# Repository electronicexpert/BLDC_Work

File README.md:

# BLDC_Work
some experiments with BLDC Motors and drivers

Thanks to Gil Vargas for the inspiration. I tried out some motors and controllers. In the end I build one myself, very close to Gil's draft.

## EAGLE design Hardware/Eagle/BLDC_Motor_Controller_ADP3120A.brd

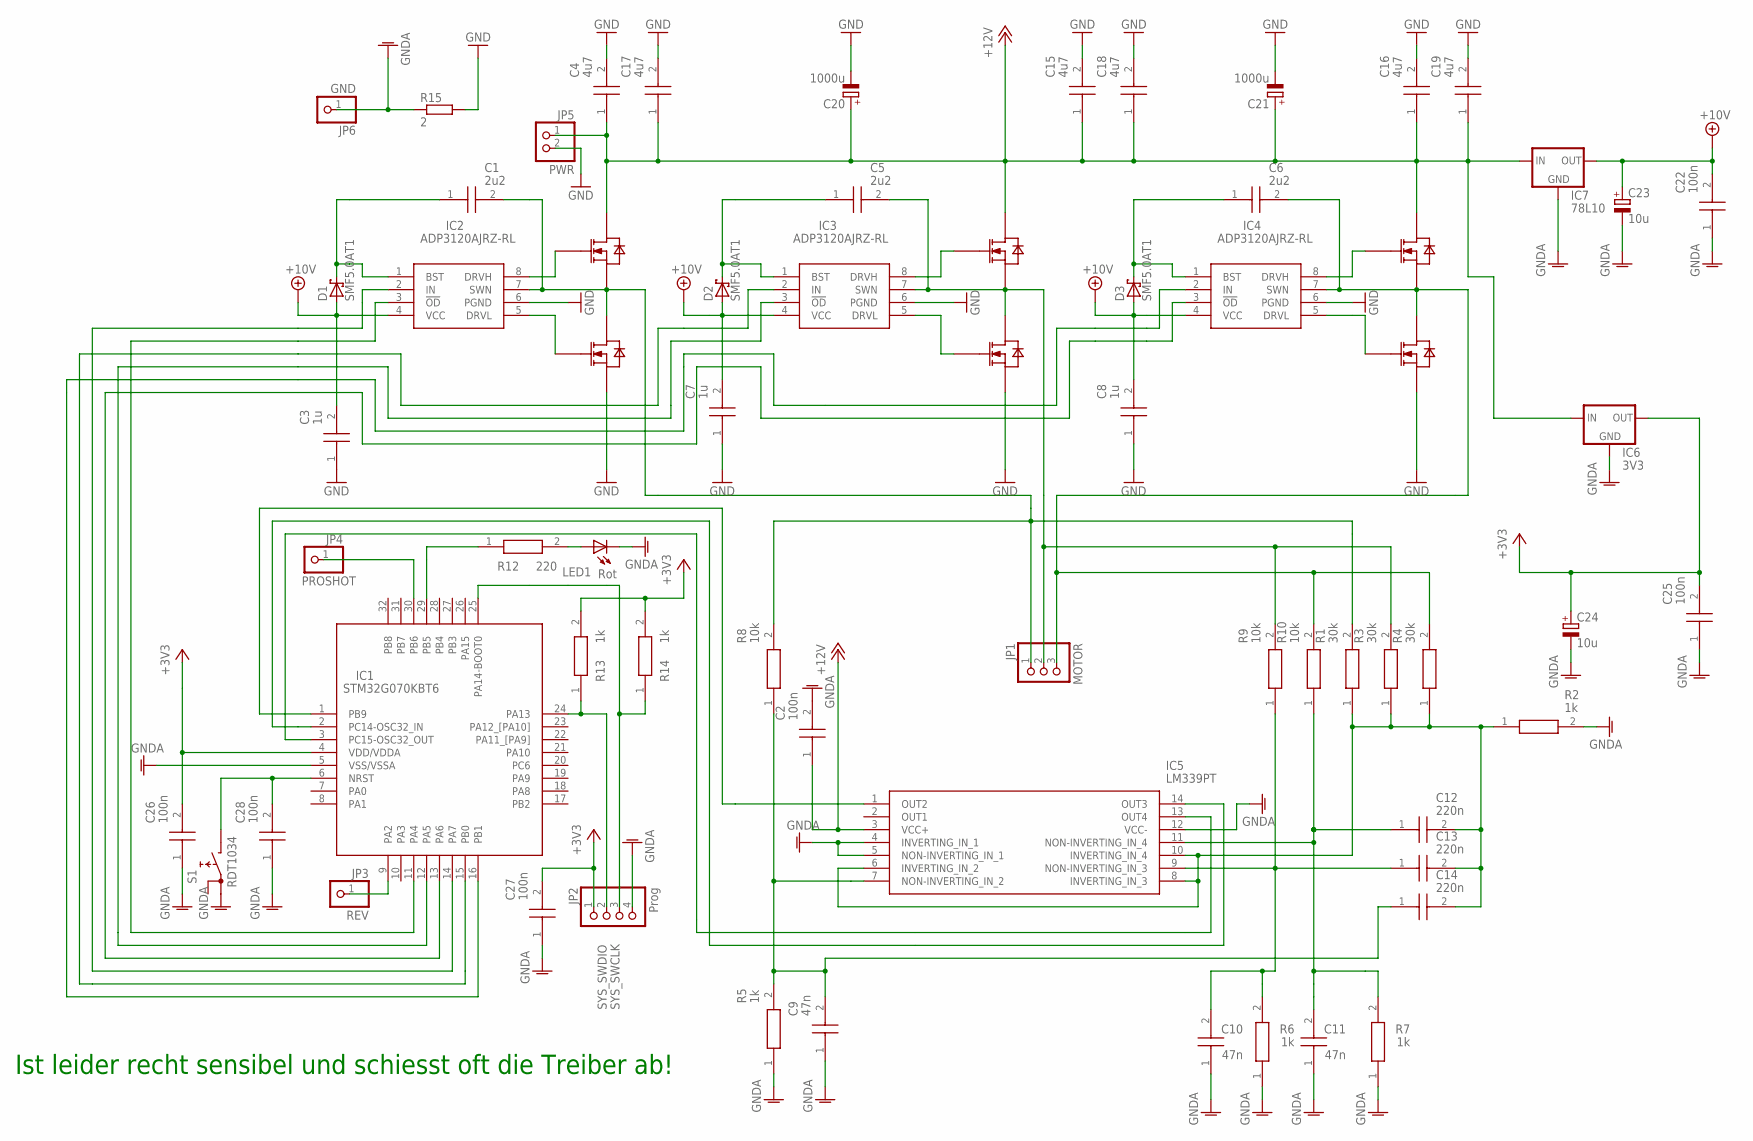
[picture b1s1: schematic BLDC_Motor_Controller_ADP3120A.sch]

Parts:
C1, C5, C6: 2u2; CAPC2012X135N
C2, C22, C25, C26, C27, C28: 100n; CAPC2012X145N
C3, C7, C8: 1u; GRM31X
C4, C15, C16, C17, C18, C19: 4u7; GRM31X
C9, C10, C11: 47n; CAPC2012X145N
C12, C13, C14: 220n; CAPC2012X145N
C20, C21: 1000u; 150CLZ-0810
C23, C24: 10u; SMC_C
D1, D2, D3: SMF5.0AT1; SOD123FL
IC1: STM32G070KBT6; QFP80P900X900X160-32N
IC2, IC3, IC4: ADP3120AJRZ-RL; SOIC127P600X175-8N
IC5: LM339PT; SOP65P640X120-14N
IC6: 3V3; SOT89R
IC7: 78L10; SOT89R
JP1: MOTOR; 1X03
JP2: Prog; 1X04
JP3: REV; 1X01
JP4: PROSHOT; 1X01
JP5: PWR; 1X02
JP6: GND; 1X01
LED1: Rot; SML0805
Q1, Q2, Q3, Q4, Q5, Q6: IRFR1205TRPBF; TO229P991X239-3_4N
R1, R3, R4: 30k; ERJUP6
R2, R5, R6, R7, R13, R14: 1k; ERJUP6
R8, R9, R10: 10k; ERJUP6
R12: 220; ERJUP6
R15: 2; R2012
S1: RDT1034

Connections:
+3V3: C24.+, C25.2, C26.2, C27.2, IC1.4 (VDD/VDDA), IC6.3 (OUT), JP2.1, R13.2, R14.2
+10V: C3.2, C7.2, C8.2, C22.2, C23.+, D1.A, D2.A, D3.A, IC2.4 (VCC), IC3.4 (VCC), IC4.4 (VCC), IC7.3 (OUT)
+12V: C2.1, C4.1, C15.1, C16.1, C17.1, C18.1, C19.1, C20.+, C21.+, IC5.3 (VCC+), IC6.2 (IN), IC7.2 (IN), JP5.1, Q1.4 (DRAIN), Q3.4 (DRAIN), Q5.4 (DRAIN)
BEMF_U: C9.2, C14.1, IC5.7 (NON-INVERTING_IN_2), R5.2, R8.1
BEMV_GND: C12.2, C13.2, C14.2, IC5.6 (INVERTING_IN_2), IC5.8 (INVERTING_IN_3), IC5.10 (INVERTING_IN_4), R1.1, R2.1, R3.1, R4.1
BEMV_V: C10.2, C13.1, IC5.9 (NON-INVERTING_IN_3), R6.2, R9.1
BEMV_W: C11.2, C12.1, IC5.11 (NON-INVERTING_IN_4), R7.2, R10.1
GND: C3.1, C4.2, C7.1, C8.1, C15.2, C16.2, C17.2, C18.2, C19.2, C20.-, C21.-, IC2.6 (PGND), IC3.6 (PGND), IC4.6 (PGND), JP5.2, Q2.3 (SOURCE), Q4.3 (SOURCE), Q6.3 (SOURCE), R15.2
GNDA: C2.2, C9.1, C10.1, C11.1, C22.1, C23.-, C24.-, C25.1, C26.1, C27.1, C28.1, IC1.5 (VSS/VSSA), IC5.4 (INVERTING_IN_1), IC5.5 (NON-INVERTING_IN_1), IC5.12 (VCC-), IC6.1 (GND), IC7.1 (GND), JP2.4, JP6.1, LED1.C, R2.2, R5.1, R6.1, R7.1, R15.1, S1.A1
IN_U: IC1.14 (PA7), IC2.2 (IN)
IN_V: IC1.15 (PB0), IC3.2 (IN)
IN_W: IC1.16 (PB1), IC4.2 (IN)
unnamed: LED1.A, R12.2
unnamed: IC3.8 (DRVH), Q3.1 (GATE)
unnamed: IC3.5 (DRVL), Q4.1 (GATE)
unnamed: IC2.8 (DRVH), Q1.1 (GATE)
unnamed: IC2.5 (DRVL), Q2.1 (GATE)
unnamed: IC4.8 (DRVH), Q5.1 (GATE)
unnamed: IC4.5 (DRVL), Q6.1 (GATE)
unnamed: C1.1, D1.C, IC2.1 (BST)
unnamed: IC1.29 (PB5), R12.1
unnamed: C5.1, D2.C, IC3.1 (BST)
unnamed: IC1.9 (PA2), JP3.1
unnamed: C6.1, D3.C, IC4.1 (BST)
unnamed: IC1.2 (PC14-OSC32_IN), IC5.14 (OUT3)
unnamed: C28.2, IC1.6 (NRST), S1.B
unnamed: IC1.1 (PB9), IC5.1 (OUT2)
unnamed: IC1.3 (PC15-OSC32_OUT), IC5.13 (OUT4)
unnamed: IC1.30 (PB6), JP4.1
OD_U: IC1.11 (PA4), IC2.3 (!OD)
OD_V: IC1.12 (PA5), IC3.3 (!OD)
OD_W: IC1.13 (PA6), IC4.3 (!OD)
SYS_SWCLK: IC1.25 (PA14-BOOT0), JP2.3, R14.1
SYS_SWDIO: IC1.24 (PA13), JP2.2, R13.1
U: C1.2, IC2.7 (SWN), JP1.1, Q1.3 (SOURCE), Q2.4 (DRAIN), R1.2, R8.2
V: C5.2, IC3.7 (SWN), JP1.2, Q3.3 (SOURCE), Q4.4 (DRAIN), R3.2, R9.2
W: C6.2, IC4.7 (SWN), JP1.3, Q5.3 (SOURCE), Q6.4 (DRAIN), R4.2, R10.2

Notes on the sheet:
Ist leider recht sensibel und schiesst oft die Treiber ab!

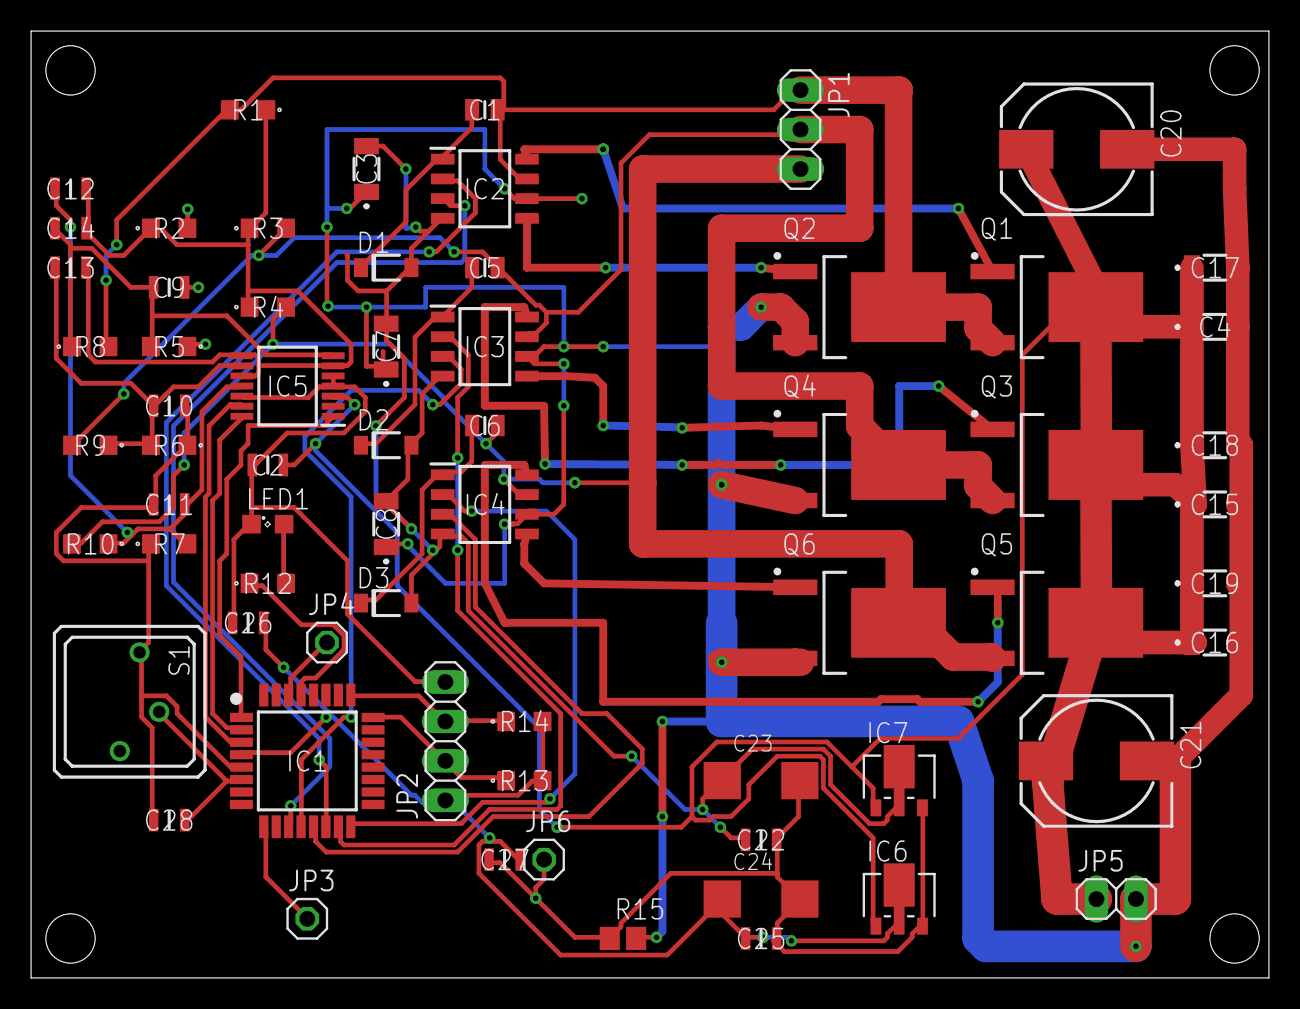
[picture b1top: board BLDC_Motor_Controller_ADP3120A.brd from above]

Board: 2 copper layers, 79.7 x 61.0 mm, 66 parts (0 on the bottom side), 37 nets.

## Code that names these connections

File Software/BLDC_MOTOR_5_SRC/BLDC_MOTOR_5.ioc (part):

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Mcu.Name=STM32G070KBTx
Mcu.Package=LQFP32
Mcu.UserName=STM32G070KBTx
PA13.Mode=Serial_Wire
PA13.Signal=SYS_SWDIO
PA14-BOOT0.Mode=Serial_Wire
PA14-BOOT0.Signal=SYS_SWCLK
PA2.GPIOParameters=GPIO_PuPd,GPIO_Label
PA2.GPIO_Label=REV
PA2.GPIO_PuPd=GPIO_PULLDOWN
PA2.Signal=GPIO_Input
PA4.GPIOParameters=GPIO_PuPd,GPIO_Label
PA4.GPIO_Label=OD_A
PA4.GPIO_PuPd=GPIO_PULLDOWN
PA4.Signal=GPIO_Output
PA5.GPIOParameters=GPIO_PuPd,GPIO_Label
PA5.GPIO_Label=OD_B
PA5.GPIO_PuPd=GPIO_PULLDOWN
PA5.Signal=GPIO_Output
PA6.GPIOParameters=GPIO_PuPd,GPIO_Label
PA6.GPIO_Label=OD_C
PA6.GPIO_PuPd=GPIO_PULLDOWN
PA6.Signal=GPIO_Output
PA7.GPIOParameters=GPIO_PuPd,GPIO_Label
PA7.GPIO_Label=PWM_A
PA7.GPIO_PuPd=GPIO_PULLDOWN
PA7.Signal=S_TIM3_CH2
PB0.GPIOParameters=GPIO_PuPd,GPIO_Label
PB0.GPIO_Label=PWM_B
PB0.GPIO_PuPd=GPIO_PULLDOWN
PB0.Signal=S_TIM3_CH3
PB1.GPIOParameters=GPIO_PuPd,GPIO_Label
PB1.GPIO_Label=PWM_C
PB1.GPIO_PuPd=GPIO_PULLDOWN
PB1.Signal=S_TIM3_CH4
PB5.GPIOParameters=GPIO_Label
PB5.GPIO_Label=LED
PB5.Signal=GPIO_Output
PB6.GPIOParameters=GPIO_Label
PB6.GPIO_Label=Proshot
PB6.Signal=S_TIM1_CH3
PB9.GPIOParameters=GPIO_PuPd,GPIO_Label,GPIO_ModeDefaultEXTI
PB9.GPIO_Label=ZC_A
PB9.GPIO_ModeDefaultEXTI=GPIO_MODE_IT_FALLING
PB9.GPIO_PuPd=GPIO_PULLUP
PB9.Signal=GPXTI9
PC14-OSC32_IN\ (PC14).GPIOParameters=GPIO_PuPd,GPIO_Label,GPIO_ModeDefaultEXTI
PC14-OSC32_IN\ (PC14).GPIO_Label=ZC_B
PC14-OSC32_IN\ (PC14).GPIO_ModeDefaultEXTI=GPIO_MODE_IT_FALLING
PC14-OSC32_IN\ (PC14).GPIO_PuPd=GPIO_PULLUP
PC14-OSC32_IN\ (PC14).Signal=GPXTI14
PC15-OSC32_OUT\ (PC15).GPIOParameters=GPIO_PuPd,GPIO_Label,GPIO_ModeDefaultEXTI
PC15-OSC32_OUT\ (PC15).GPIO_Label=ZC_C
PC15-OSC32_OUT\ (PC15).GPIO_ModeDefaultEXTI=GPIO_MODE_IT_FALLING
PC15-OSC32_OUT\ (PC15).GPIO_PuPd=GPIO_PULLUP
PC15-OSC32_OUT\ (PC15).Signal=GPXTI15
RCC.HSE_VALUE=8000000
RCC.SYSCLKFreq_VALUE=64000000
RCC.SYSCLKSource=RCC_SYSCLKSOURCE_PLLCLK
board=custom

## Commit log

2024-08-16 Create Run of control program
2024-08-16 Create test
2024-09-04 Create Mehrkanal_OC_Simple
